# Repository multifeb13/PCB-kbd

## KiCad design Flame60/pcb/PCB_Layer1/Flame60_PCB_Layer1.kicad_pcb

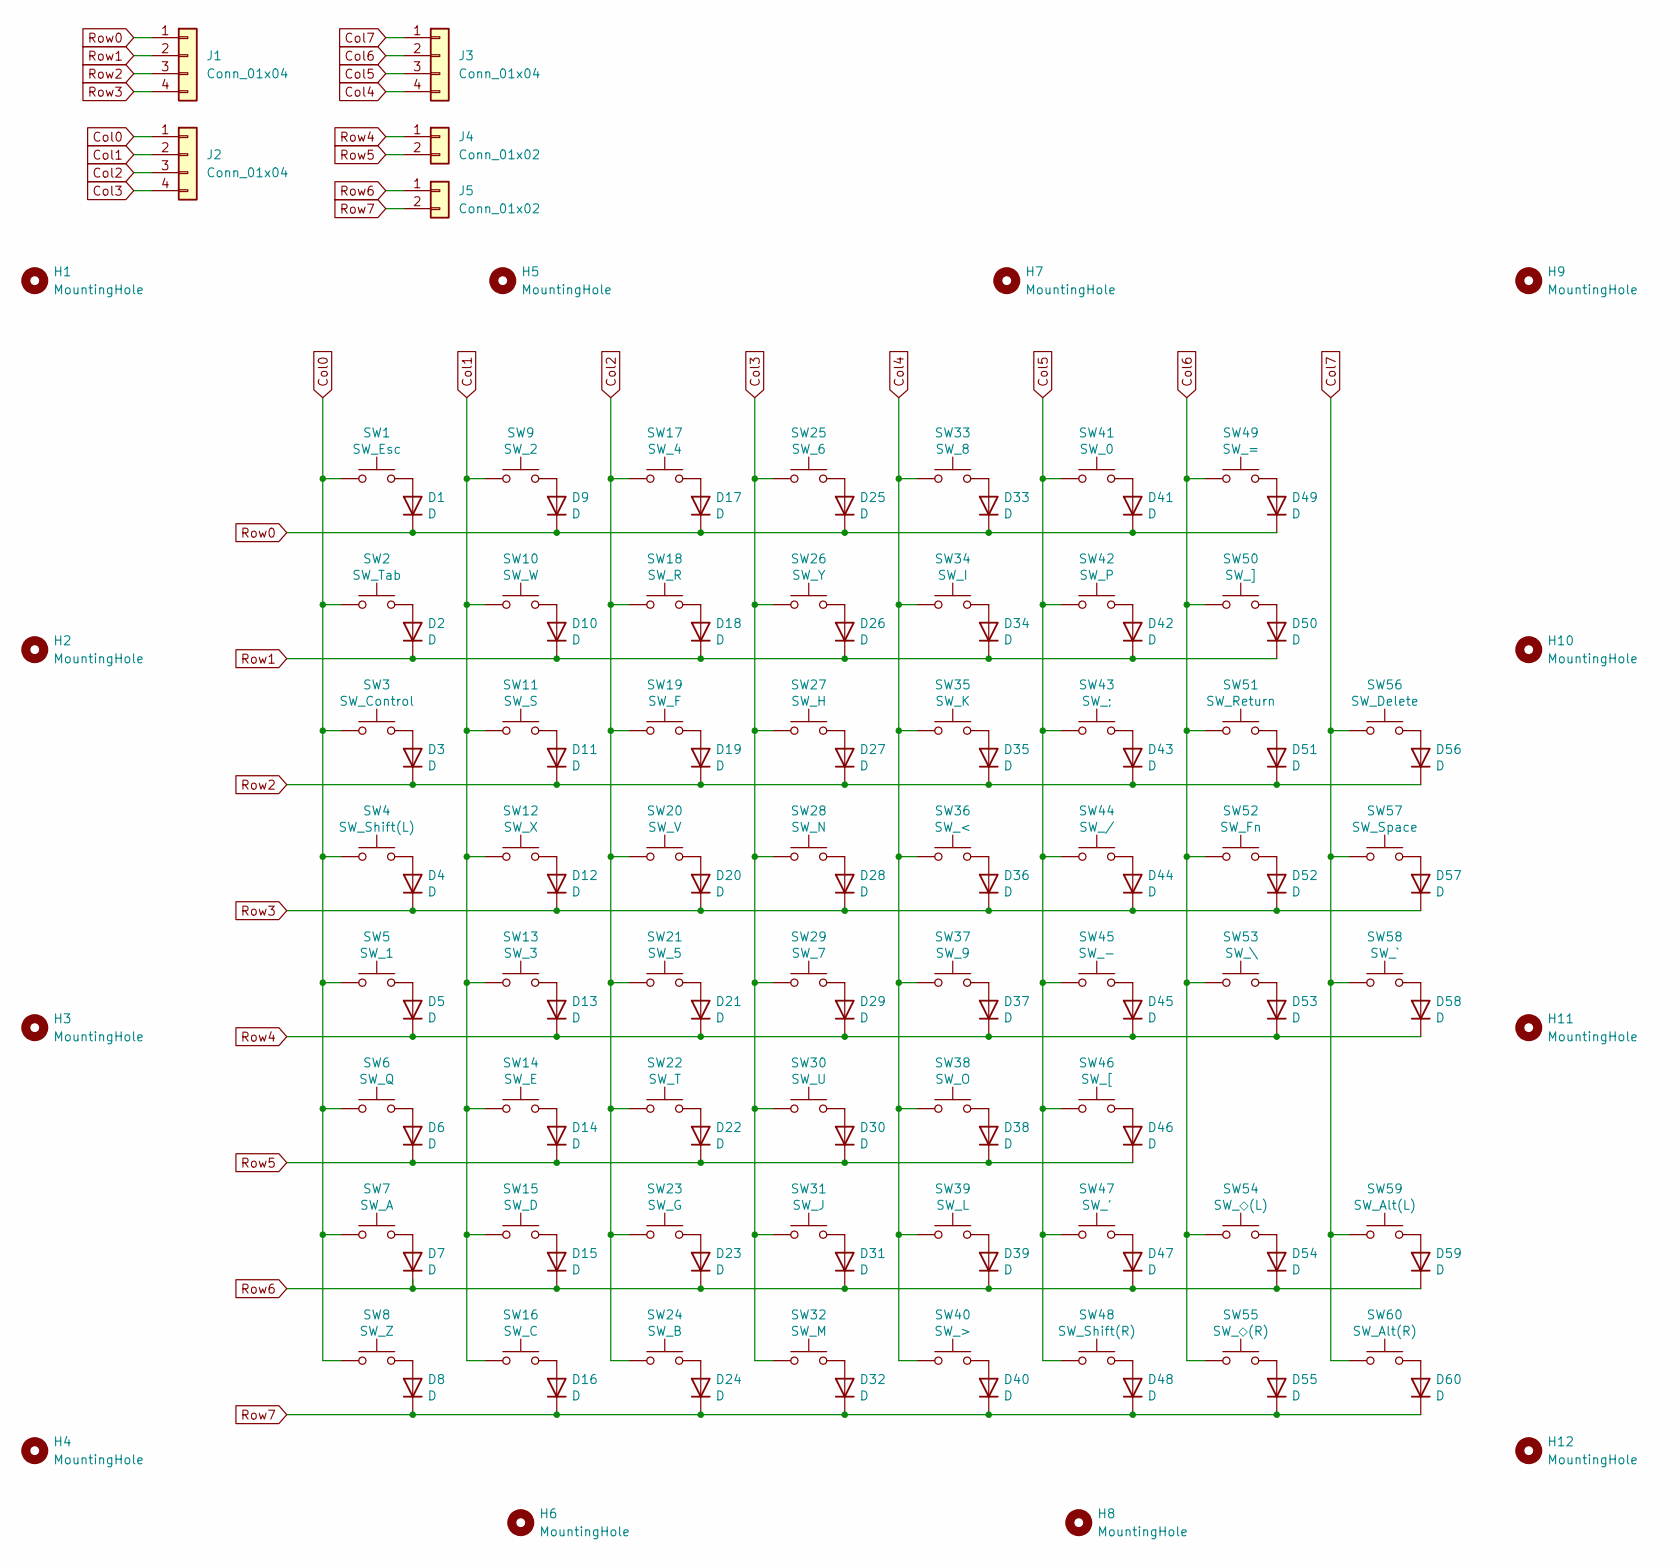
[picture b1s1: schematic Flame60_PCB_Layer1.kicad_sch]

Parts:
D1, D2, D3, D4, D5, D6, D7, D8, D9, D10, D11, D12, D13, D14, D15, D16, D17, D18, D19, D20, D21, D22, D23, D24, D25, D26, D27, D28, D29, D30, D31, D32, D33, D34, D35, D36, D37, D38, D39, D40, D41, D42, D43, D44, D45, D46, D47, D48, D49, D50, D51, D52, D53, D54, D55, D56, D57, D58, D59, D60: D; Diode_TH_SMD
H1, H2, H3, H4, H5, H6, H7, H8, H9, H10, H11, H12: MountingHole; m2_Screw_Hole
J1, J2, J3: Conn_01x04; PinHeader_1x04_P2.54mm_Vertical
J4, J5: Conn_01x02; PinHeader_1x02_P2.54mm_Vertical
SW1: SW_Esc; CherryMX_Solder_1u
SW2: SW_Tab; CherryMX_Solder_1.5u
SW3: SW_Control; CherryMX_Solder_1.75u
SW4: SW_Shift(L); CherryMX_Solder_2.25u
SW5: SW_1; CherryMX_Solder_1u
SW6: SW_Q; CherryMX_Solder_1u
SW7: SW_A; CherryMX_Solder_1u
SW8: SW_Z; CherryMX_Solder_1u
SW9: SW_2; CherryMX_Solder_1u
SW10: SW_W; CherryMX_Solder_1u
SW11: SW_S; CherryMX_Solder_1u
SW12: SW_X; CherryMX_Solder_1u
SW13: SW_3; CherryMX_Solder_1u
SW14: SW_E; CherryMX_Solder_1u
SW15: SW_D; CherryMX_Solder_1u
SW16: SW_C; CherryMX_Solder_1u
SW17: SW_4; CherryMX_Solder_1u
SW18: SW_R; CherryMX_Solder_1u
SW19: SW_F; CherryMX_Solder_1u
SW20: SW_V; CherryMX_Solder_1u
SW21: SW_5; CherryMX_Solder_1u
SW22: SW_T; CherryMX_Solder_1u
SW23: SW_G; CherryMX_Solder_1u
SW24: SW_B; CherryMX_Solder_1u
SW25: SW_6; CherryMX_Solder_1u
SW26: SW_Y; CherryMX_Solder_1u
SW27: SW_H; CherryMX_Solder_1u
SW28: SW_N; CherryMX_Solder_1u
SW29: SW_7; CherryMX_Solder_1u
SW30: SW_U; CherryMX_Solder_1u
SW31: SW_J; CherryMX_Solder_1u
SW32: SW_M; CherryMX_Solder_1u
SW33: SW_8; CherryMX_Solder_1u
SW34: SW_I; CherryMX_Solder_1u
SW35: SW_K; CherryMX_Solder_1u
SW36: SW_<; CherryMX_Solder_1u
SW37: SW_9; CherryMX_Solder_1u
SW38: SW_O; CherryMX_Solder_1u
SW39: SW_L; CherryMX_Solder_1u
SW40: SW_>; CherryMX_Solder_1u
SW41: SW_0; CherryMX_Solder_1u
SW42: SW_P; CherryMX_Solder_1u
SW43: SW_;; CherryMX_Solder_1u
SW44: SW_/; CherryMX_Solder_1u
SW45: SW_-; CherryMX_Solder_1u
SW46: SW_[; CherryMX_Solder_1u
SW47: SW_'; CherryMX_Solder_1u
SW48: SW_Shift(R); CherryMX_Solder_1.75u
SW49: SW_=; CherryMX_Solder_1u
SW50: SW_]; CherryMX_Solder_1u
SW51: SW_Return; CherryMX_Solder_2.25u
SW52: SW_Fn; CherryMX_Solder_1u
SW53: SW_\; CherryMX_Solder_1u
SW54: SW_◇(L); CherryMX_Solder_1.5u
SW55: SW_◇(R); CherryMX_Solder_1.5u
SW56: SW_Delete; CherryMX_Solder_1.5u
SW57: SW_Space; CherryMX_Solder_6u
SW58: SW_`; CherryMX_Solder_1u
SW59: SW_Alt(L); CherryMX_Solder_1u
SW60: SW_Alt(R); CherryMX_Solder_1u

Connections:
Col0: J2.1, SW1.1, SW2.1, SW3.1, SW4.1, SW5.1, SW6.1, SW7.1, SW8.1
Col1: J2.2, SW9.1, SW10.1, SW11.1, SW12.1, SW13.1, SW14.1, SW15.1, SW16.1
Col2: J2.3, SW17.1, SW18.1, SW19.1, SW20.1, SW21.1, SW22.1, SW23.1, SW24.1
Col3: J2.4, SW25.1, SW26.1, SW27.1, SW28.1, SW29.1, SW30.1, SW31.1, SW32.1
Col4: J3.4, SW33.1, SW34.1, SW35.1, SW36.1, SW37.1, SW38.1, SW39.1, SW40.1
Col5: J3.3, SW41.1, SW42.1, SW43.1, SW44.1, SW45.1, SW46.1, SW47.1, SW48.1
Col6: J3.2, SW49.1, SW50.1, SW51.1, SW52.1, SW53.1, SW54.1, SW55.1
Col7: J3.1, SW56.1, SW57.1, SW58.1, SW59.1, SW60.1
unnamed: D1.2 (A), SW1.2
unnamed: D2.2 (A), SW2.2
unnamed: D3.2 (A), SW3.2
unnamed: D4.2 (A), SW4.2
unnamed: D5.2 (A), SW5.2
unnamed: D6.2 (A), SW6.2
unnamed: D7.2 (A), SW7.2
unnamed: D8.2 (A), SW8.2
unnamed: D9.2 (A), SW9.2
unnamed: D10.2 (A), SW10.2
unnamed: D11.2 (A), SW11.2
unnamed: D12.2 (A), SW12.2
unnamed: D13.2 (A), SW13.2
unnamed: D14.2 (A), SW14.2
unnamed: D15.2 (A), SW15.2
unnamed: D16.2 (A), SW16.2
unnamed: D17.2 (A), SW17.2
unnamed: D18.2 (A), SW18.2
unnamed: D19.2 (A), SW19.2
unnamed: D20.2 (A), SW20.2
unnamed: D21.2 (A), SW21.2
unnamed: D22.2 (A), SW22.2
unnamed: D23.2 (A), SW23.2
unnamed: D24.2 (A), SW24.2
unnamed: D25.2 (A), SW25.2
unnamed: D26.2 (A), SW26.2
unnamed: D27.2 (A), SW27.2
unnamed: D28.2 (A), SW28.2
unnamed: D29.2 (A), SW29.2
unnamed: D30.2 (A), SW30.2
unnamed: D31.2 (A), SW31.2
unnamed: D32.2 (A), SW32.2
unnamed: D33.2 (A), SW33.2
unnamed: D34.2 (A), SW34.2
unnamed: D35.2 (A), SW35.2
unnamed: D36.2 (A), SW36.2
unnamed: D37.2 (A), SW37.2
unnamed: D38.2 (A), SW38.2
unnamed: D39.2 (A), SW39.2
unnamed: D40.2 (A), SW40.2
unnamed: D41.2 (A), SW41.2
unnamed: D42.2 (A), SW42.2
unnamed: D43.2 (A), SW43.2
unnamed: D44.2 (A), SW44.2
unnamed: D45.2 (A), SW45.2
unnamed: D46.2 (A), SW46.2
unnamed: D47.2 (A), SW47.2
unnamed: D48.2 (A), SW48.2
unnamed: D49.2 (A), SW49.2
unnamed: D50.2 (A), SW50.2
unnamed: D51.2 (A), SW51.2
unnamed: D52.2 (A), SW52.2
unnamed: D53.2 (A), SW53.2
unnamed: D54.2 (A), SW54.2
unnamed: D55.2 (A), SW55.2
unnamed: D56.2 (A), SW56.2
unnamed: D57.2 (A), SW57.2
unnamed: D58.2 (A), SW58.2
unnamed: D59.2 (A), SW59.2
unnamed: D60.2 (A), SW60.2
Row0: D1.1 (K), D9.1 (K), D17.1 (K), D25.1 (K), D33.1 (K), D41.1 (K), D49.1 (K), J1.1
Row1: D2.1 (K), D10.1 (K), D18.1 (K), D26.1 (K), D34.1 (K), D42.1 (K), D50.1 (K), J1.2
Row2: D3.1 (K), D11.1 (K), D19.1 (K), D27.1 (K), D35.1 (K), D43.1 (K), D51.1 (K), D56.1 (K), J1.3
Row3: D4.1 (K), D12.1 (K), D20.1 (K), D28.1 (K), D36.1 (K), D44.1 (K), D52.1 (K), D57.1 (K), J1.4
Row4: D5.1 (K), D13.1 (K), D21.1 (K), D29.1 (K), D37.1 (K), D45.1 (K), D53.1 (K), D58.1 (K), J4.1
Row5: D6.1 (K), D14.1 (K), D22.1 (K), D30.1 (K), D38.1 (K), D46.1 (K), J4.2
Row6: D7.1 (K), D15.1 (K), D23.1 (K), D31.1 (K), D39.1 (K), D47.1 (K), D54.1 (K), D59.1 (K), J5.1
Row7: D8.1 (K), D16.1 (K), D24.1 (K), D32.1 (K), D40.1 (K), D48.1 (K), D55.1 (K), D60.1 (K), J5.2

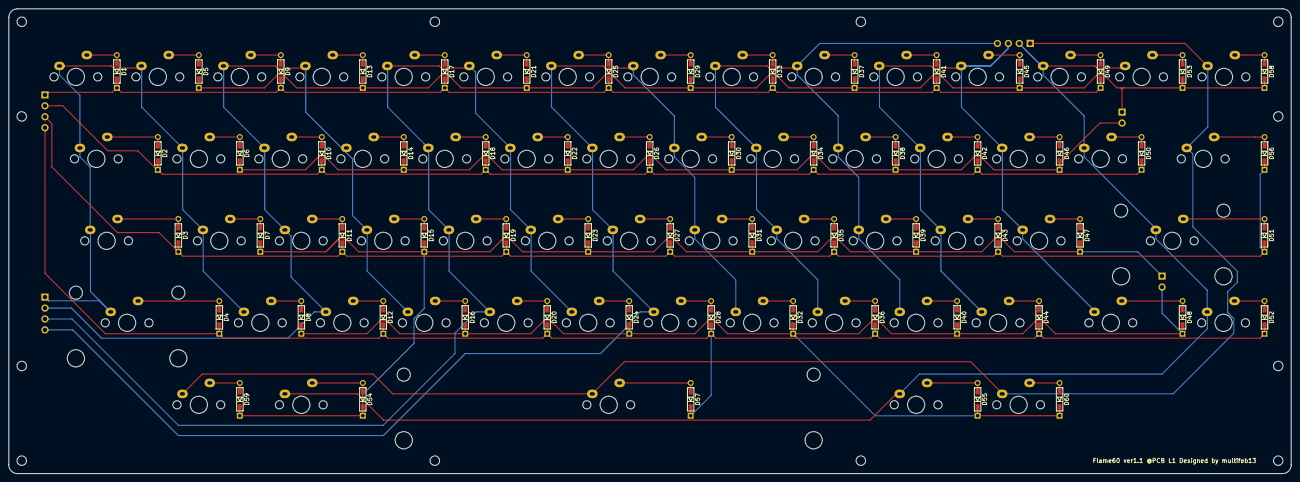
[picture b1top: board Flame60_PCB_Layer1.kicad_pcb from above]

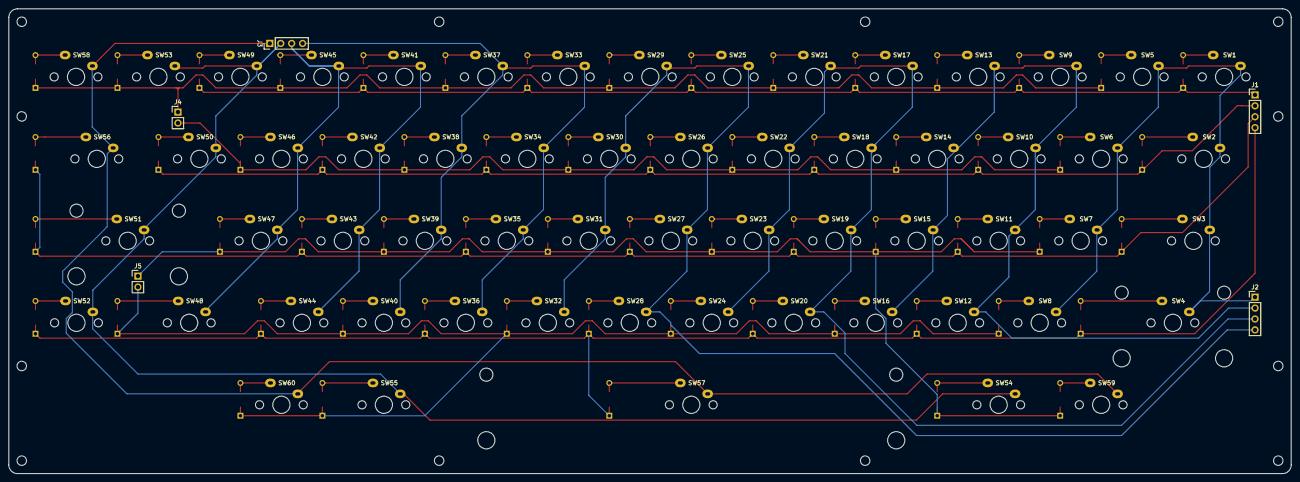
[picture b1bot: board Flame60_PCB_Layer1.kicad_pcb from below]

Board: 2 copper layers, 298.0 x 108.0 mm, 137 parts (65 on the bottom side), 76 nets.

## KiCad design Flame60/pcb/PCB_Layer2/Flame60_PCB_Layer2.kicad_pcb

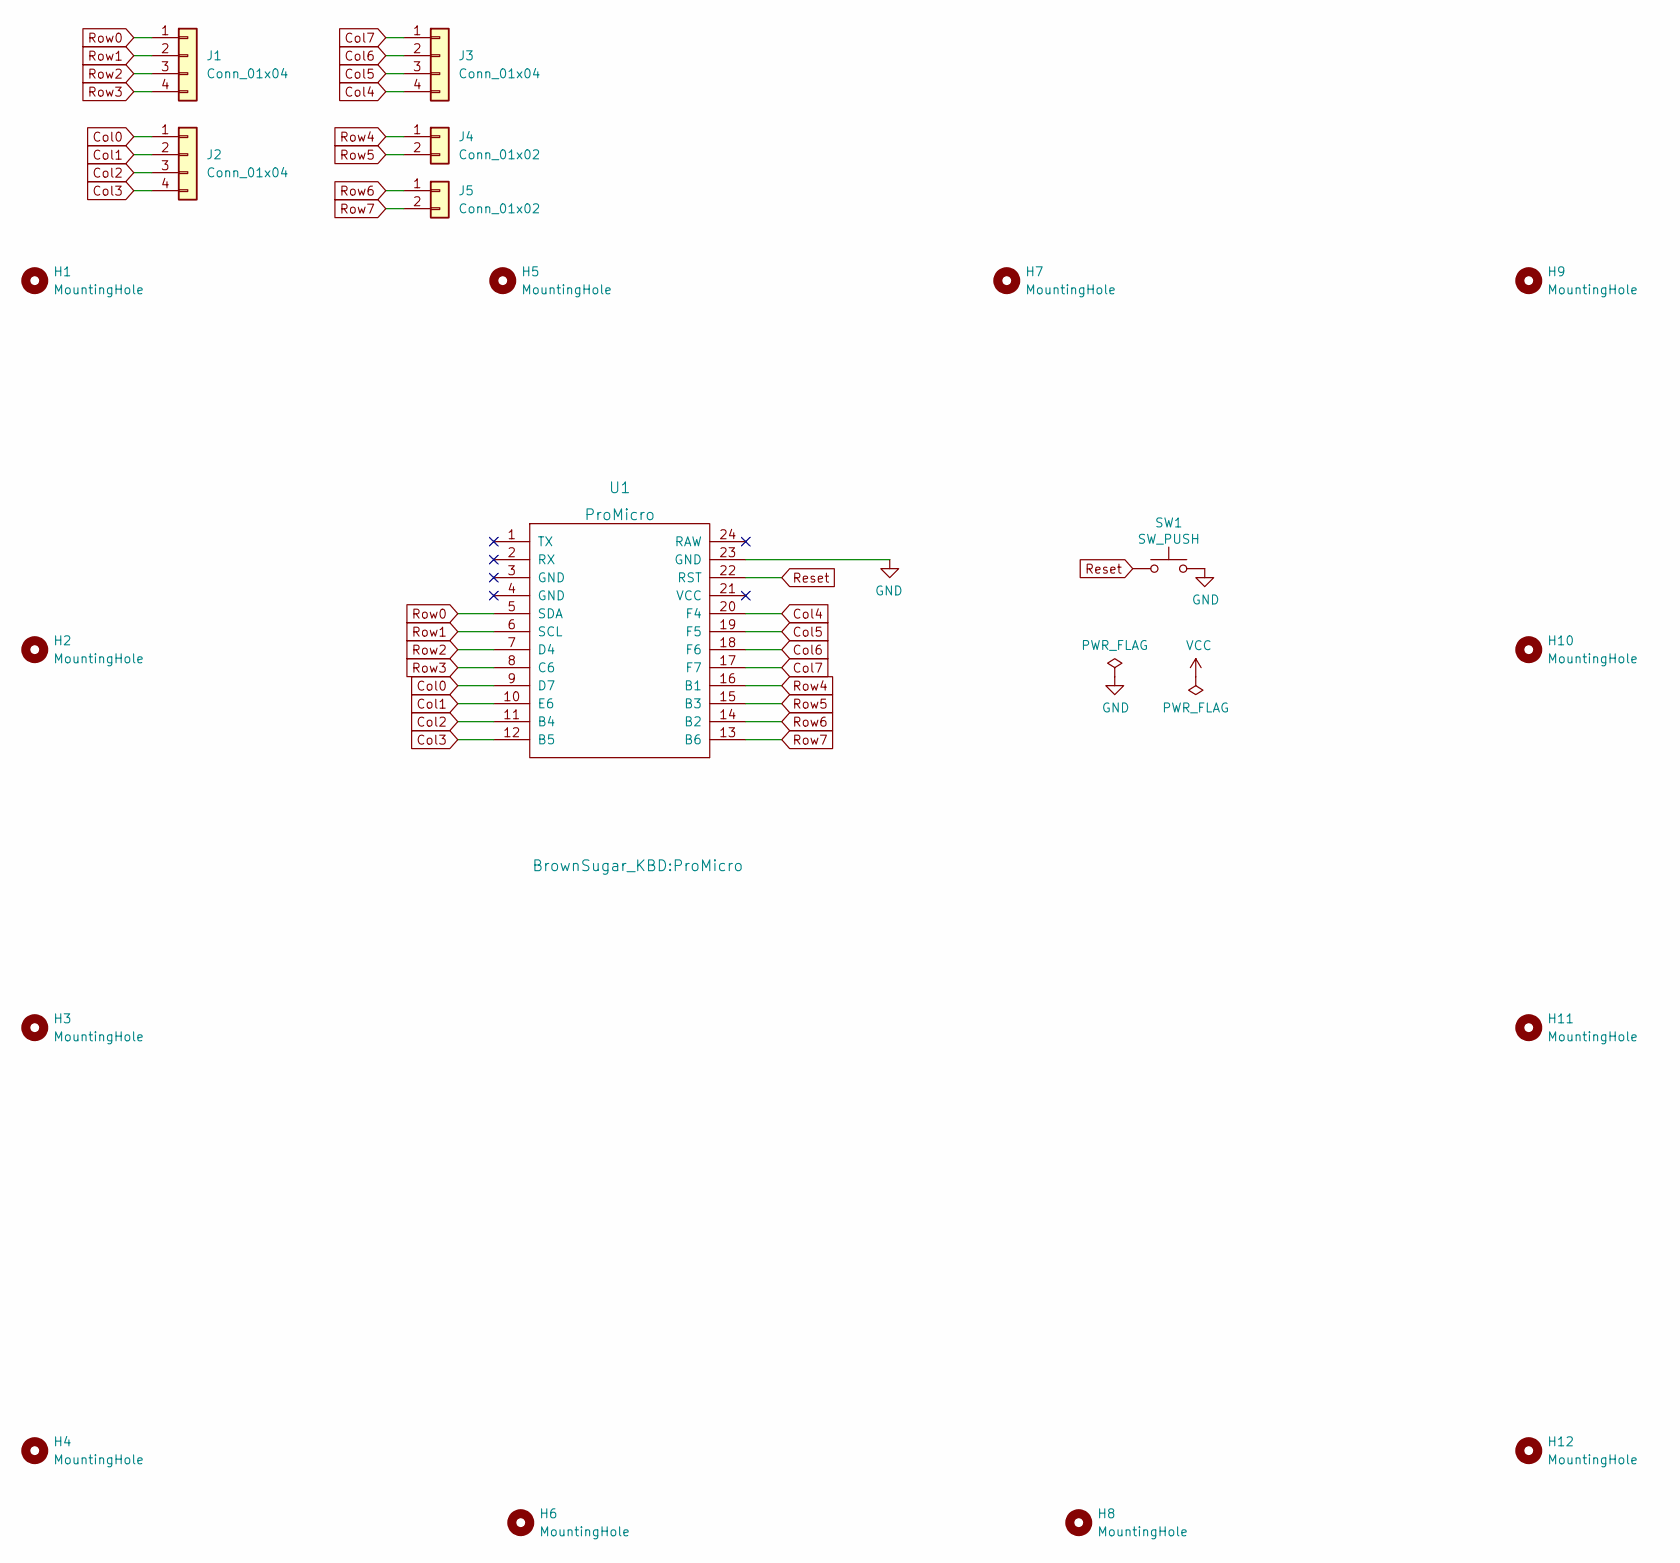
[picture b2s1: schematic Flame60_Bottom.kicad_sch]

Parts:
H1, H2, H3, H4, H5, H6, H7, H8, H9, H10, H11, H12: MountingHole; m2_Screw_Hole
J1, J2, J3: Conn_01x04; PinSocket_1x04_P2.54mm_Vertical
J4, J5: Conn_01x02; PinSocket_1x02_P2.54mm_Vertical
SW1: SW_PUSH; SW_107193_SKHHLPA010
U1: ProMicro

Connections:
Col0: J2.1, U1.9 (D7)
Col1: J2.2, U1.10 (E6)
Col2: J2.3, U1.11 (B4)
Col3: J2.4, U1.12 (B5)
Col4: J3.4, U1.20 (F4)
Col5: J3.3, U1.19 (F5)
Col6: J3.2, U1.18 (F6)
Col7: J3.1, U1.17 (F7)
GND: SW1.2, U1.23 (GND)
Reset: SW1.1, U1.22 (RST)
Row0: J1.1, U1.5 (SDA)
Row1: J1.2, U1.6 (SCL)
Row2: J1.3, U1.7 (D4)
Row3: J1.4, U1.8 (C6)
Row4: J4.1, U1.16 (B1)
Row5: J4.2, U1.15 (B3)
Row6: J5.1, U1.14 (B2)
Row7: J5.2, U1.13 (B6)

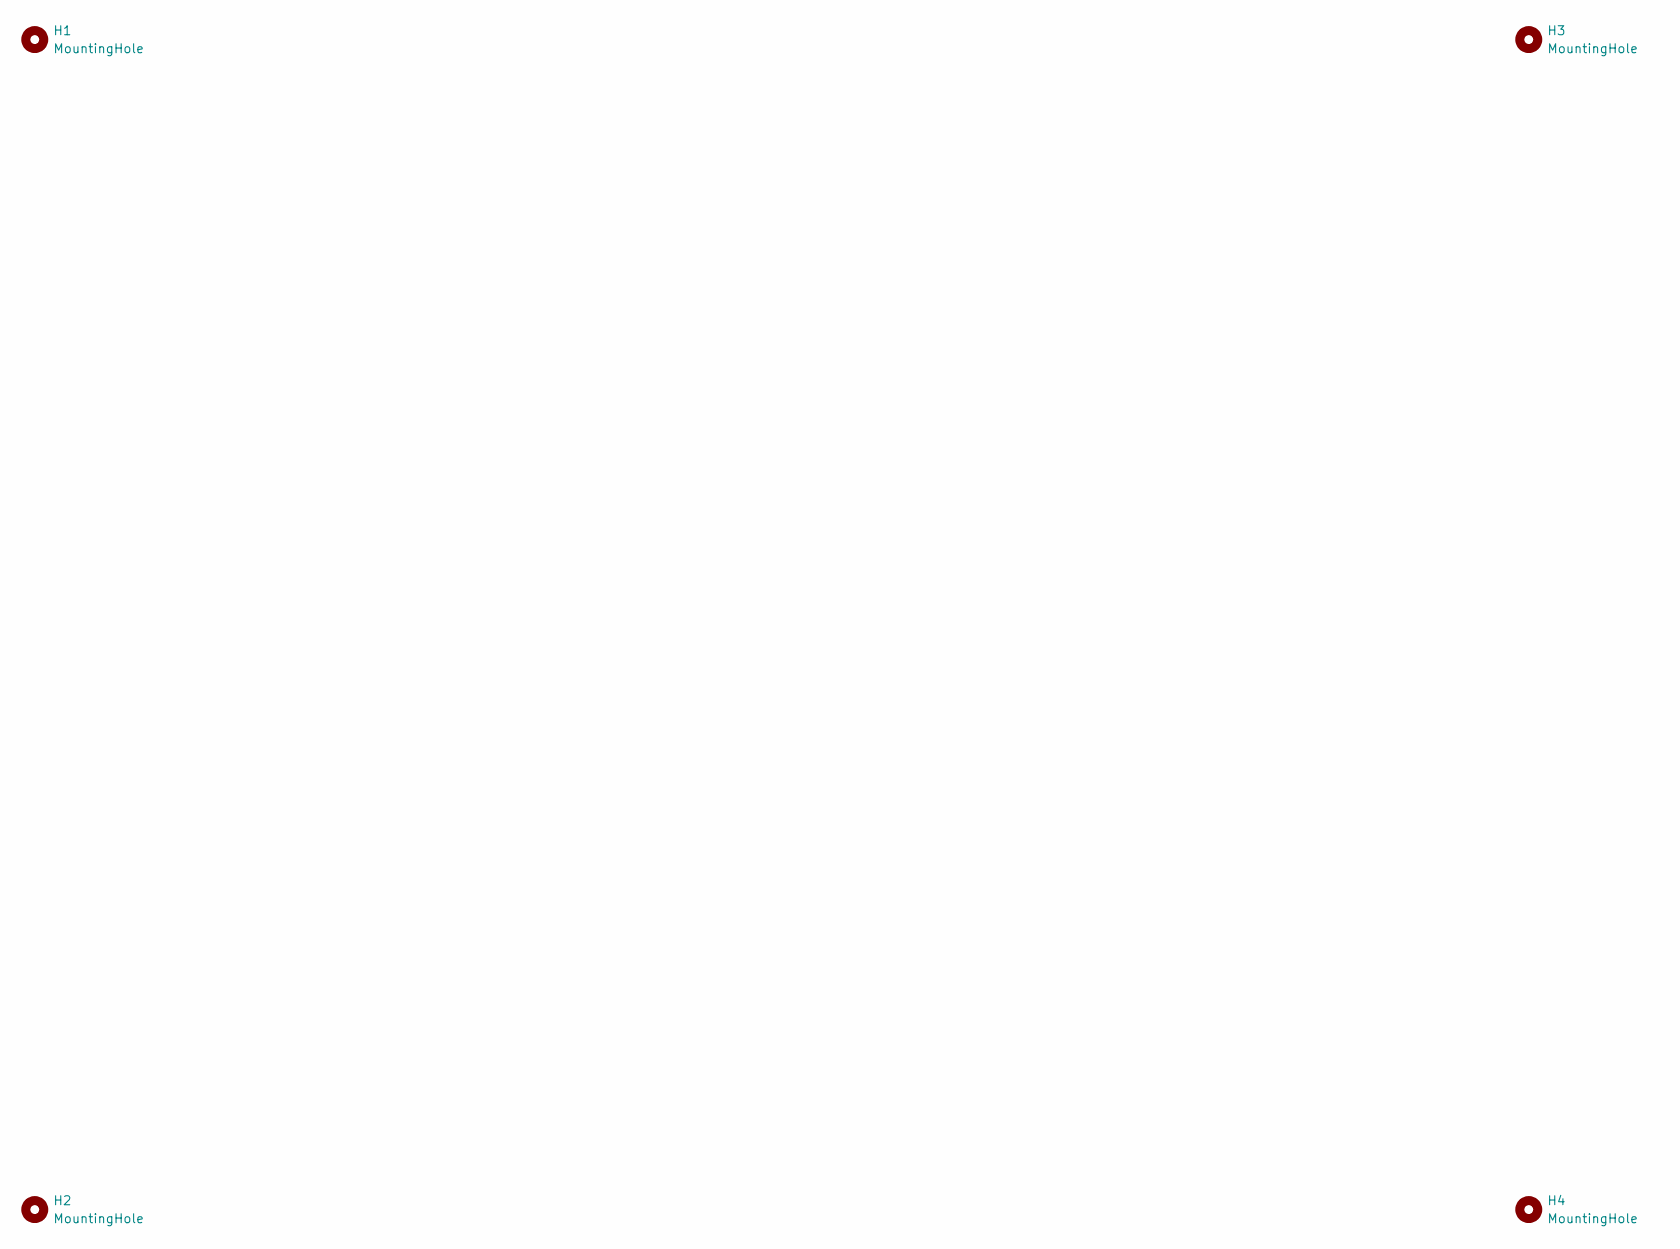
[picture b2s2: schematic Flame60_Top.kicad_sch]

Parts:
H1, H2, H3, H4: MountingHole; m2_Screw_Hole

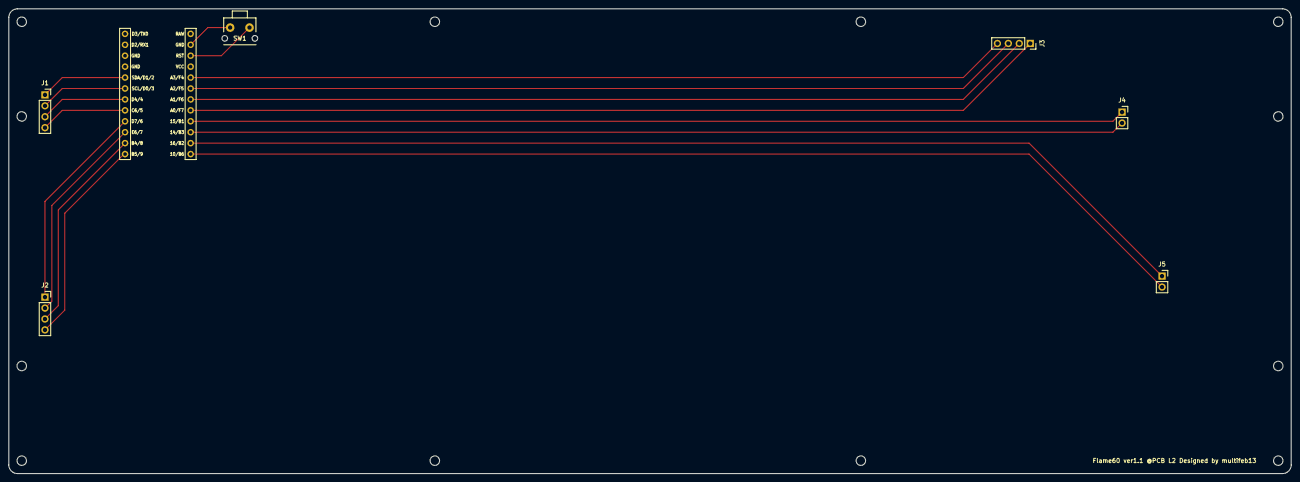
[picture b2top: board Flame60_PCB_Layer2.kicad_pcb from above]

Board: 2 copper layers, 298.0 x 108.0 mm, 19 parts (0 on the bottom side), 18 nets.

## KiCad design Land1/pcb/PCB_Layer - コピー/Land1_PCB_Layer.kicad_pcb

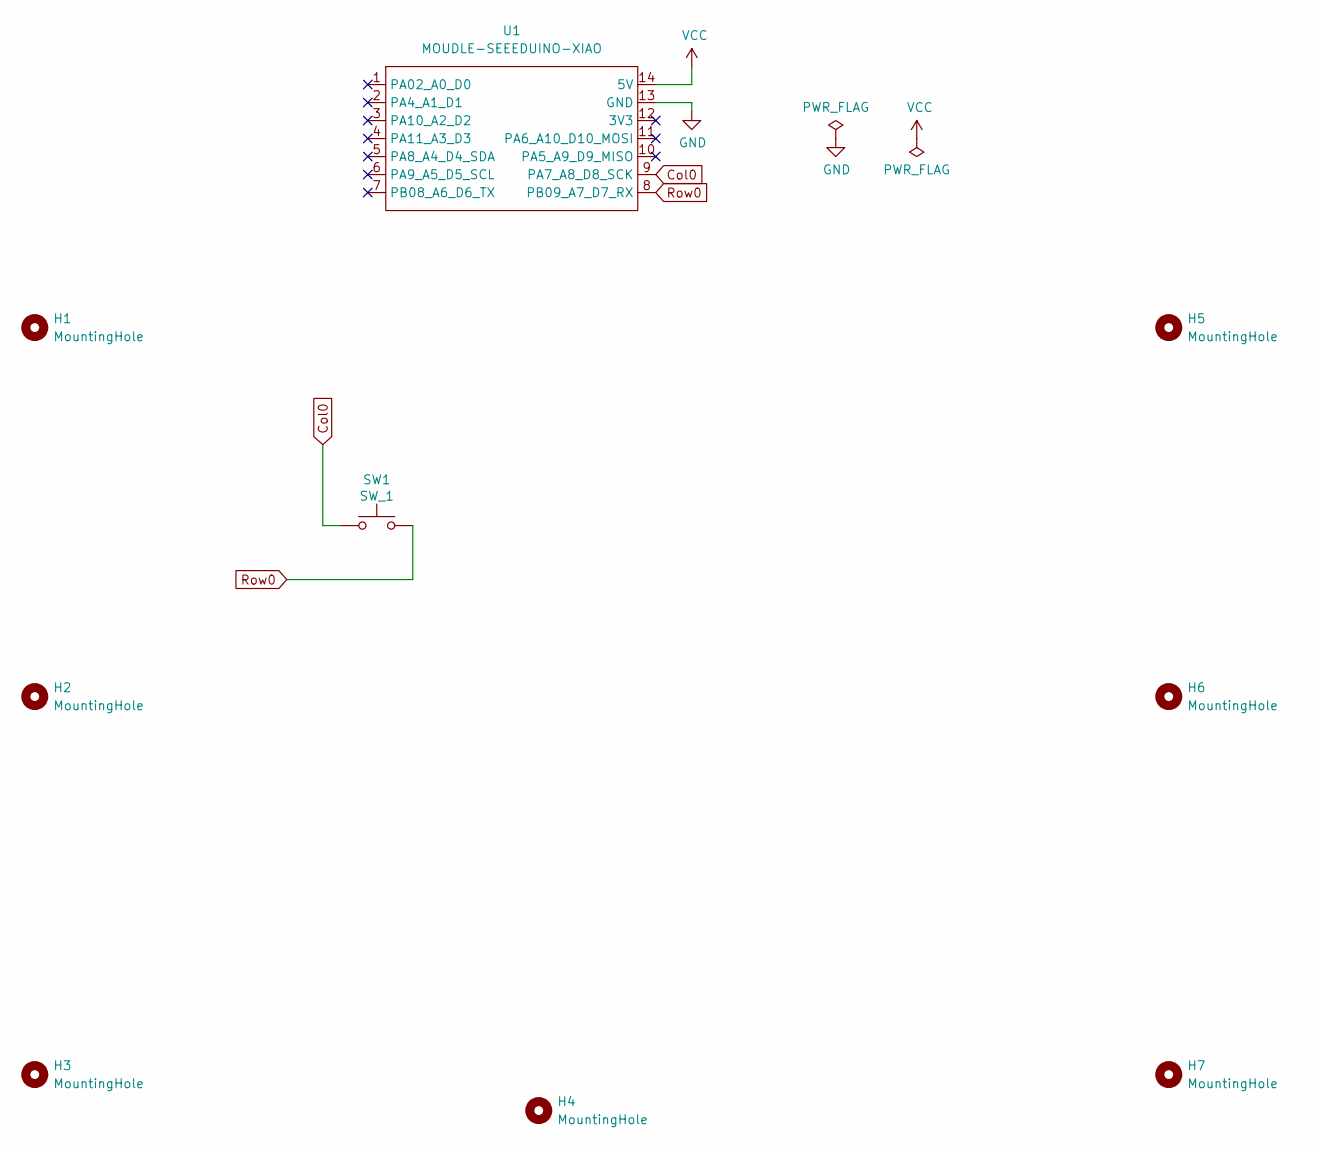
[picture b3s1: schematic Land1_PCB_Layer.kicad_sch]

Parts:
H1, H2, H3, H4, H5, H6, H7: MountingHole; m2_Screw_Hole
SW1: SW_1; CherryMX_Solder_1u
U1: MOUDLE-SEEEDUINO-XIAO; XIAO-RP2040-inside-only_Cutout

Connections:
Col0: SW1.1, U1.9 (PA7_A8_D8_SCK)
GND: U1.13 (GND)
Row0: SW1.2, U1.8 (PB09_A7_D7_RX)
VCC: U1.14 (5V)

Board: 2 copper layers, 9 parts (1 on the bottom side), 2 nets, no tracks yet.

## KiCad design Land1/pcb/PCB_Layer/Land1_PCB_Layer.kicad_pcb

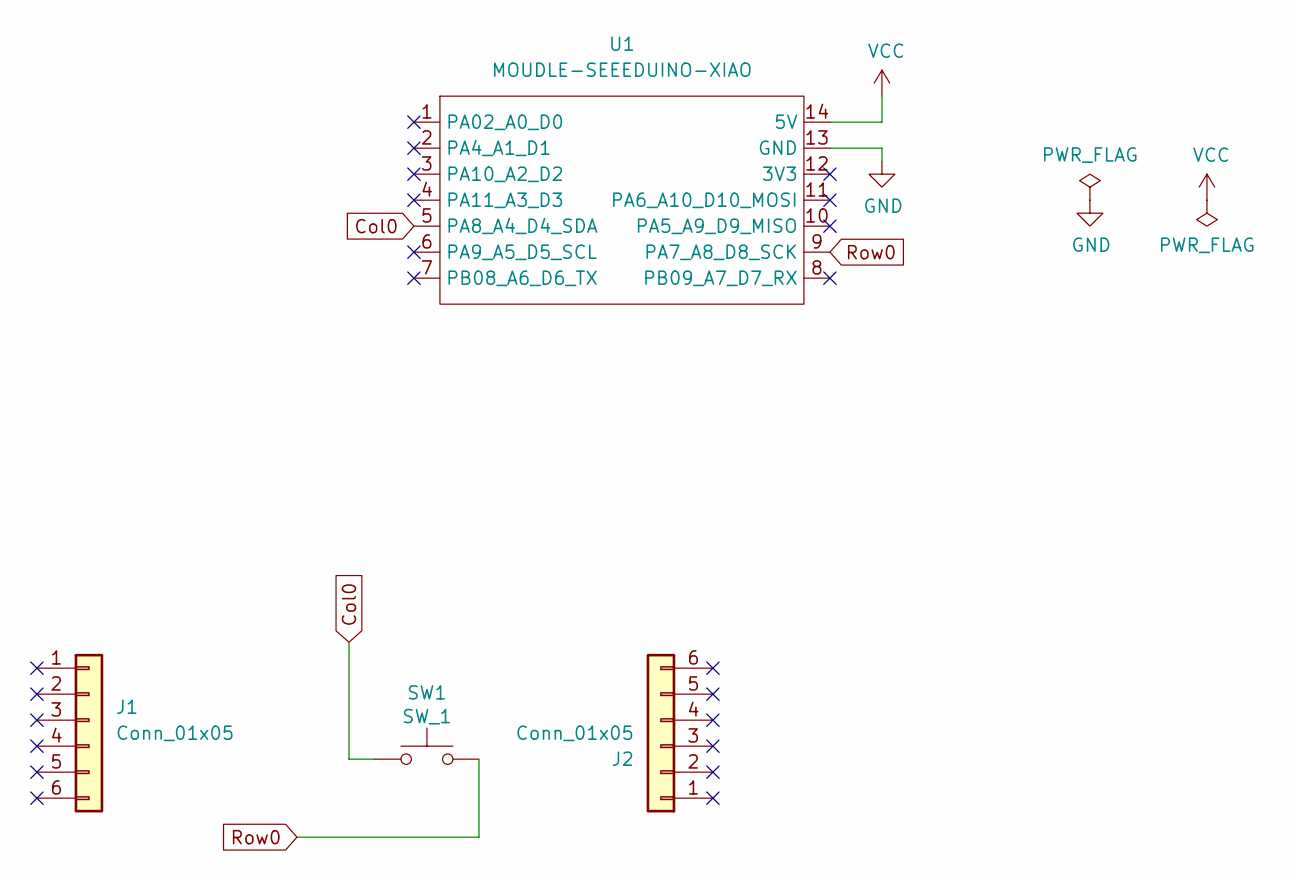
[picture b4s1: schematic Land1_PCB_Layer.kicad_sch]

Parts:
J1, J2: Conn_01x05; PinSocket_1x06_P2.54mm_Vertical
SW1: SW_1; CherryMX_Solder_1u
U1: MOUDLE-SEEEDUINO-XIAO; XIAO-RP2040-inside-only_Cutout

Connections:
Col0: SW1.1, U1.5 (PA8_A4_D4_SDA)
GND: U1.13 (GND)
Row0: SW1.2, U1.9 (PA7_A8_D8_SCK)
VCC: U1.14 (5V)

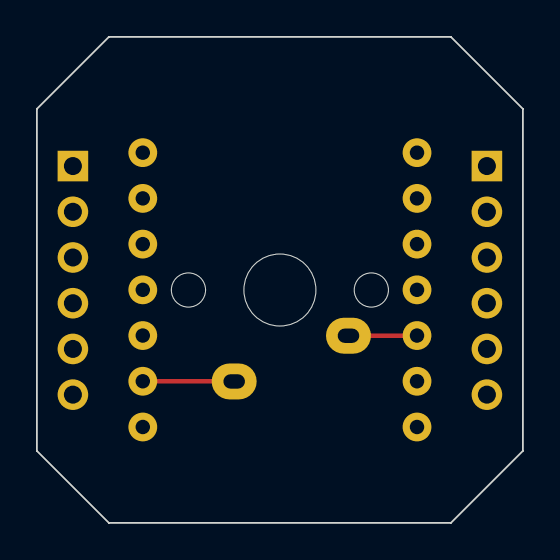
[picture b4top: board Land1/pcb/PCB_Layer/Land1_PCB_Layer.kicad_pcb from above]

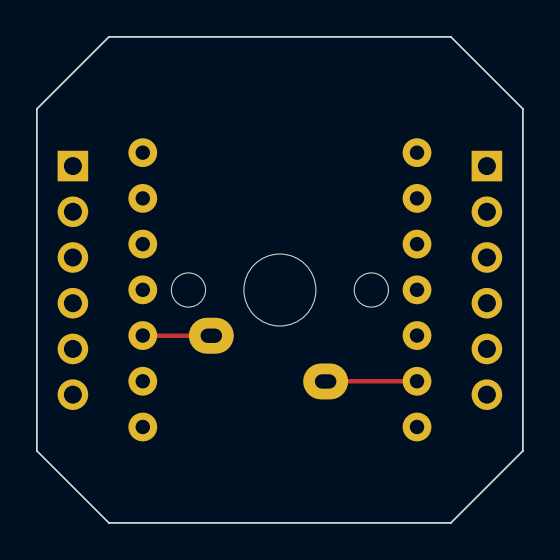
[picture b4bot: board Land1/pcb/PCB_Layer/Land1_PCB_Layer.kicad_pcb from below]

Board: 2 copper layers, 27.0 x 27.0 mm, 4 parts (3 on the bottom side), 2 nets.
